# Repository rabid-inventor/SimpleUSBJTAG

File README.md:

# SimpleUSBJTAG
A simple USB to jtag board based on the CH552 MCU running code from Diodep https://github.com/diodep/ch55x_jtag

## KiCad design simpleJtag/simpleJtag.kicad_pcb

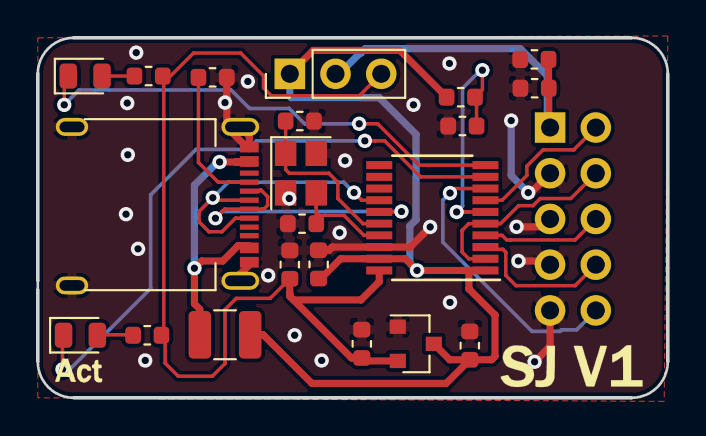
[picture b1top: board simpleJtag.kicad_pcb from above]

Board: 2 copper layers, 35.0 x 20.0 mm, 23 parts (1 on the bottom side), 20 nets.

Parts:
C1, C2, C5, C7: 1uF; C_0603_1608Metric
C3, C6: 0.1uF; C_0603_1608Metric
C4: 0.1uf; C_0603_1608Metric
C8, C9: 22pf; C_0603_1608Metric
D1, D2: LED; LED_0805_2012Metric
F1: Polyfuse_Small; C_1210_3225Metric
J1: Conn_02x05_Odd_Even; Multicomp_MC9A22-1034_2x05x2.54mm_Angled
JP1: Jumper_NC_Dual; PinHeader_1x03_P2.54mm_Vertical
P1: USB_C_Plug; usbc_16pos_lugged_allsmt
R1: 56K; R_0603_1608Metric
R2, R3: 330R; R_0603_1608Metric
R4: R_Small; R_0603_1608Metric
TP1: RESET; TestPoint_Pad_D2.5mm
U1: AP7333-33SRG-7; SOT-23
U2: CH552T; TSSOP-20_4.4x6.5mm_Pitch0.65mm
Y1: Crystal_GND24; Crystal_SMD_3225-4Pin_3.2x2.5mm

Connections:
+3V3: C2.1, C3.1, JP1.3, R2.1, R3.1, U1.2, U2.20
/J_RESET: J1.10, U2.8
/RESET: C7.2, R4.2, TP1.1, U2.6
/TCK: J1.4, U2.2, U2.5
/TDI: J1.8, U2.3
/TDO: J1.6, U2.4
/TMS: J1.2, U2.7
/TVCC: C5.1, C6.1, J1.1, JP1.2
/USBD+: P1.A6, P1.B6, U2.14
/USBD-: P1.A7, P1.B7, U2.15
GND: C1.2, C2.2, C3.2, C4.2, C5.2, C6.2, C8.2, C9.2, J1.3, J1.5, J1.7, J1.9, P1.A1, P1.A12, P1.B1, P1.B12, P1.S1, R1.1, R4.1, U1.1, U2.18, Y1.2, Y1.4
unnamed: C8.1, U2.16, Y1.1
unnamed: C9.1, U2.17, Y1.3
unnamed: D1.1, U2.10
unnamed: D1.2, R2.2
unnamed: D2.1, U2.9
unnamed: D2.2, R3.2
unnamed: F1.2, P1.A4, P1.A9, P1.B4, P1.B9
unnamed: P1.A5, R1.2
VBUS: C1.1, C4.1, C7.1, F1.1, JP1.1, U1.3, U2.1, U2.19

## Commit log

2020-02-15 started basic layout work
2020-02-15 end of day sync
2020-02-21 more schmatics work routing almost complete
2020-02-22 swapping USBC plug to USBC socket
2020-02-27 Routing v1 complete drc done ready for FAB
2020-02-27 made gerbers
